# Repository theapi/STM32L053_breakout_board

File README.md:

# STM32L053_breakout_board
Breakout board for the STM32L053

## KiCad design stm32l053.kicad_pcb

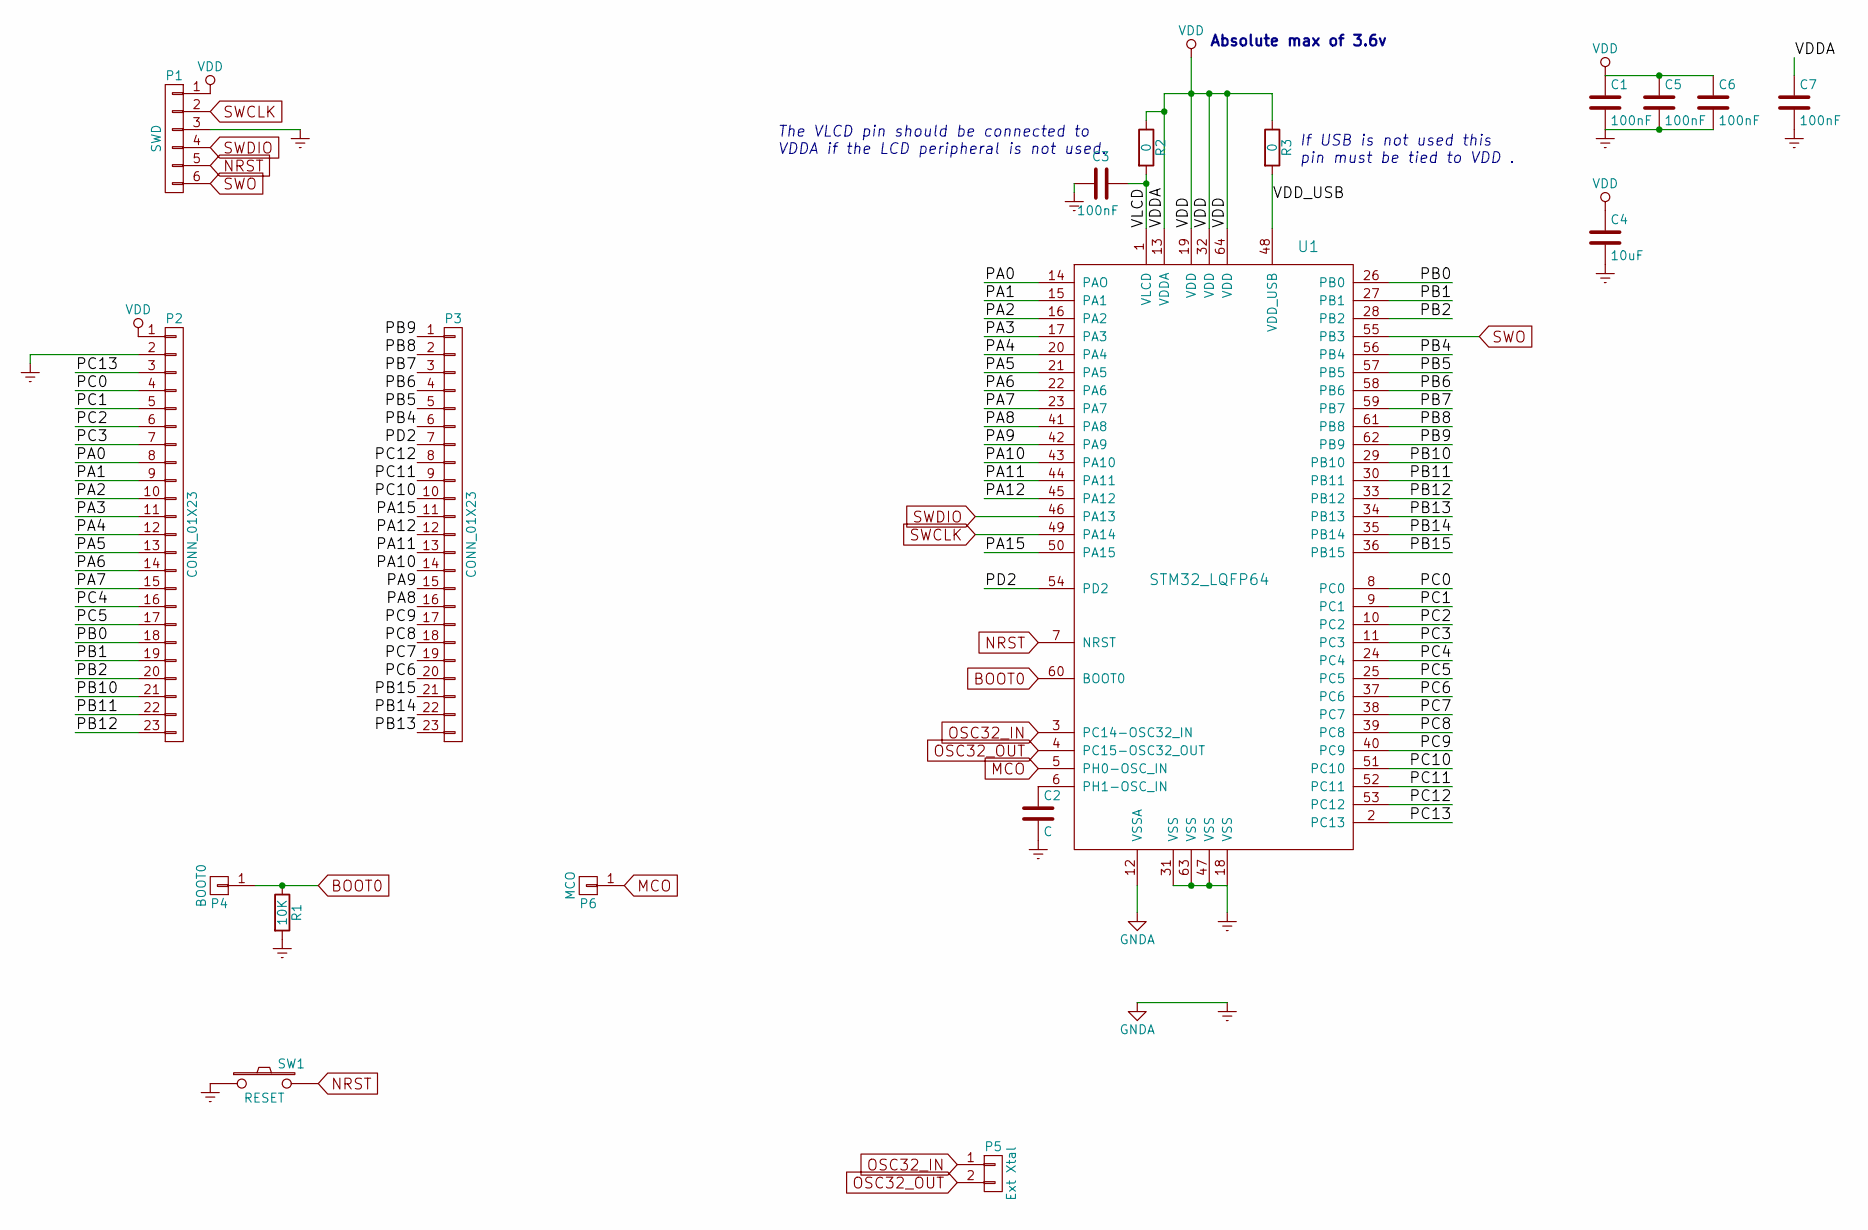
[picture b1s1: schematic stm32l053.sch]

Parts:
C1, C3, C5, C6, C7: 100nF; C_0805_HandSoldering
C2: C; C_0805_HandSoldering
C4: 10uF; C_0805_HandSoldering
P1: SWD; Pin_Header_Straight_1x06
P2, P3: CONN_01X23; Pin_Header_Straight_1x23
P4: BOOT0; Measurement_Point_Round-SMD-Pad_Small
P5: Ext Xtal; Crystal_SMD_0603_2Pads_obsolete
P6: MCO; Measurement_Point_Round-SMD-Pad_Small
R1: 10K; R_0805_HandSoldering
R2, R3: 0; R_0805_HandSoldering
SW1: RESET; SW_PUSH_6mm
U1: STM32_LQFP64; LQFP-64_10x10mm_Pitch0.5mm

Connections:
/PA0: P2.8, U1.14 (PAO)
/PA1: P2.9, U1.15 (PA1)
/PA2: P2.10, U1.16 (PA2)
/PA3: P2.11, U1.17 (PA3)
/PA4: P2.12, U1.20 (PA4)
/PA5: P2.13, U1.21 (PA5)
/PA6: P2.14, U1.22 (PA6)
/PA7: P2.15, U1.23 (PA7)
/PA8: P3.16, U1.41 (PA8)
/PA9: P3.15, U1.42 (PA9)
/PA10: P3.14, U1.43 (PA10)
/PA11: P3.13, U1.44 (PA11)
/PA12: P3.12, U1.45 (PA12)
/PA15: P3.11, U1.50 (PA15)
/PB0: P2.18, U1.26 (PB0)
/PB1: P2.19, U1.27 (PB1)
/PB2: P2.20, U1.28 (PB2)
/PB4: P3.6, U1.56 (PB4)
/PB5: P3.5, U1.57 (PB5)
/PB6: P3.4, U1.58 (PB6)
/PB7: P3.3, U1.59 (PB7)
/PB8: P3.2, U1.61 (PB8)
/PB9: P3.1, U1.62 (PB9)
/PB10: P2.21, U1.29 (PB10)
/PB11: P2.22, U1.30 (PB11)
/PB12: P2.23, U1.33 (PB12)
/PB13: P3.23, U1.34 (PB13)
/PB14: P3.22, U1.35 (PB14)
/PB15: P3.21, U1.36 (PB15)
/PC0: P2.4, U1.8 (PC0)
/PC1: P2.5, U1.9 (PC1)
/PC2: P2.6, U1.10 (PC2)
/PC3: P2.7, U1.11 (PC3)
/PC4: P2.16, U1.24 (PC4)
/PC5: P2.17, U1.25 (PC5)
/PC6: P3.20, U1.37 (PC6)
/PC7: P3.19, U1.38 (PC7)
/PC8: P3.18, U1.39 (PC8)
/PC9: P3.17, U1.40 (PC9)
/PC10: P3.10, U1.51 (PC10)
/PC11: P3.9, U1.52 (PC11)
/PC12: P3.8, U1.53 (PC12)
/PC13: P2.3, U1.2 (PC13)
/PD2: P3.7, U1.54 (PD2)
/VDD_USB: R3.2, U1.48 (VDD_USB)
/VLCD: C3.2, R2.2, U1.1 (VLCD)
BOOT0: P4.1, R1.1, U1.60 (BOOT0)
Earth: C1.2, C2.2, C3.1, C4.2, C5.2, C6.2, C7.2, P1.3, P2.2, R1.2, SW1.1, U1.12 (VSSA), U1.18 (VSS), U1.31 (VSS), U1.47 (VSS), U1.63 (VSS)
MCO: P6.1, U1.5 (PH0-OSC_IN)
NRST: P1.5, SW1.2, U1.7 (NRST)
unnamed: C2.1, U1.6 (PH1-OSC_IN)
OSC32_IN: P5.1, U1.3 (PC14-OSC32_IN)
OSC32_OUT: P5.2, U1.4 (PC15-OSC32_OUT)
SWCLK: P1.2, U1.49 (PA14)
SWDIO: P1.4, U1.46 (PA13)
SWO: P1.6, U1.55 (PB3)
VDD: C1.1, C4.1, C5.1, C6.1, C7.1, P1.1, P2.1, R2.1, R3.1, U1.13 (VDDA), U1.19 (VDD), U1.32 (VDD), U1.64 (VDD)

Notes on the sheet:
The VLCD pin should be connected to VDDA if the LCD peripheral is not used.
If USB is not used this pin must be tied to VDD .
Absolute max of 3.6v

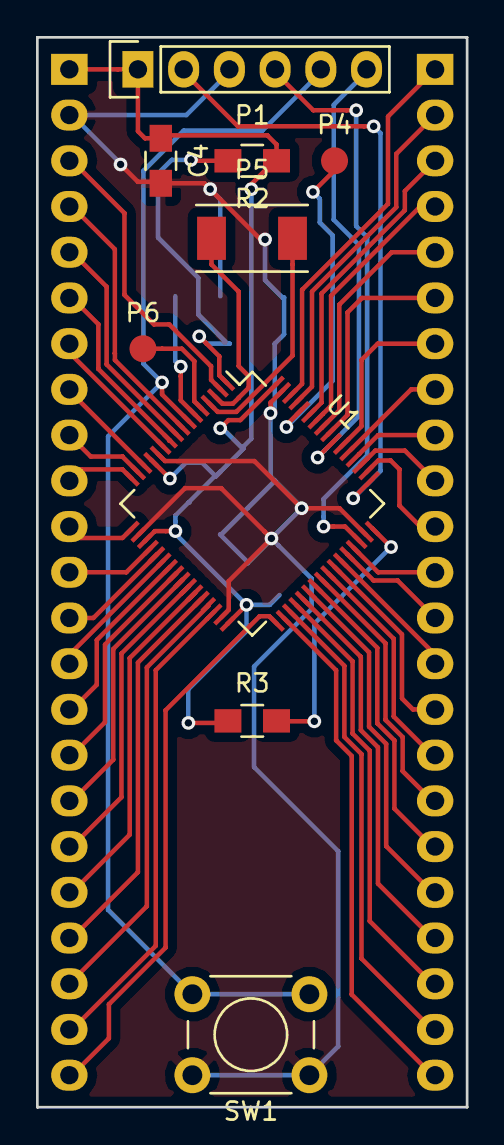
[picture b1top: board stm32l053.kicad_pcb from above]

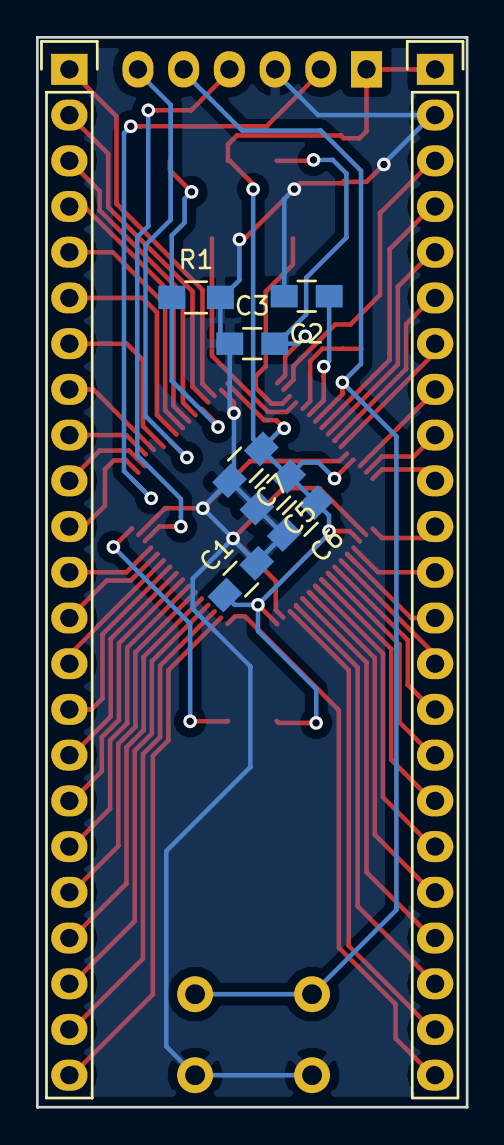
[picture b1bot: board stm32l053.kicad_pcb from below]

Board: 2 copper layers, 23.9 x 59.4 mm, 18 parts (9 on the bottom side), 57 nets.

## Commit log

2016-10-16 Power
2016-10-16 SWO connector
2016-10-16 PA header
2016-10-16 PB header
2016-10-16 23 pin headers
2016-10-16 10uF cap
2016-10-16 Restart layout
2016-10-16 Design rules
2016-10-16 Changing header layout to match pins on mcu
2016-10-16 Simpler layout
2016-10-17 GPIO initial routing
2016-10-17 Flipped the headers to the back
2016-10-17 SWO header
2016-10-17 VDD connected
2016-10-17 Earth connected
2016-10-17 Ground plane
